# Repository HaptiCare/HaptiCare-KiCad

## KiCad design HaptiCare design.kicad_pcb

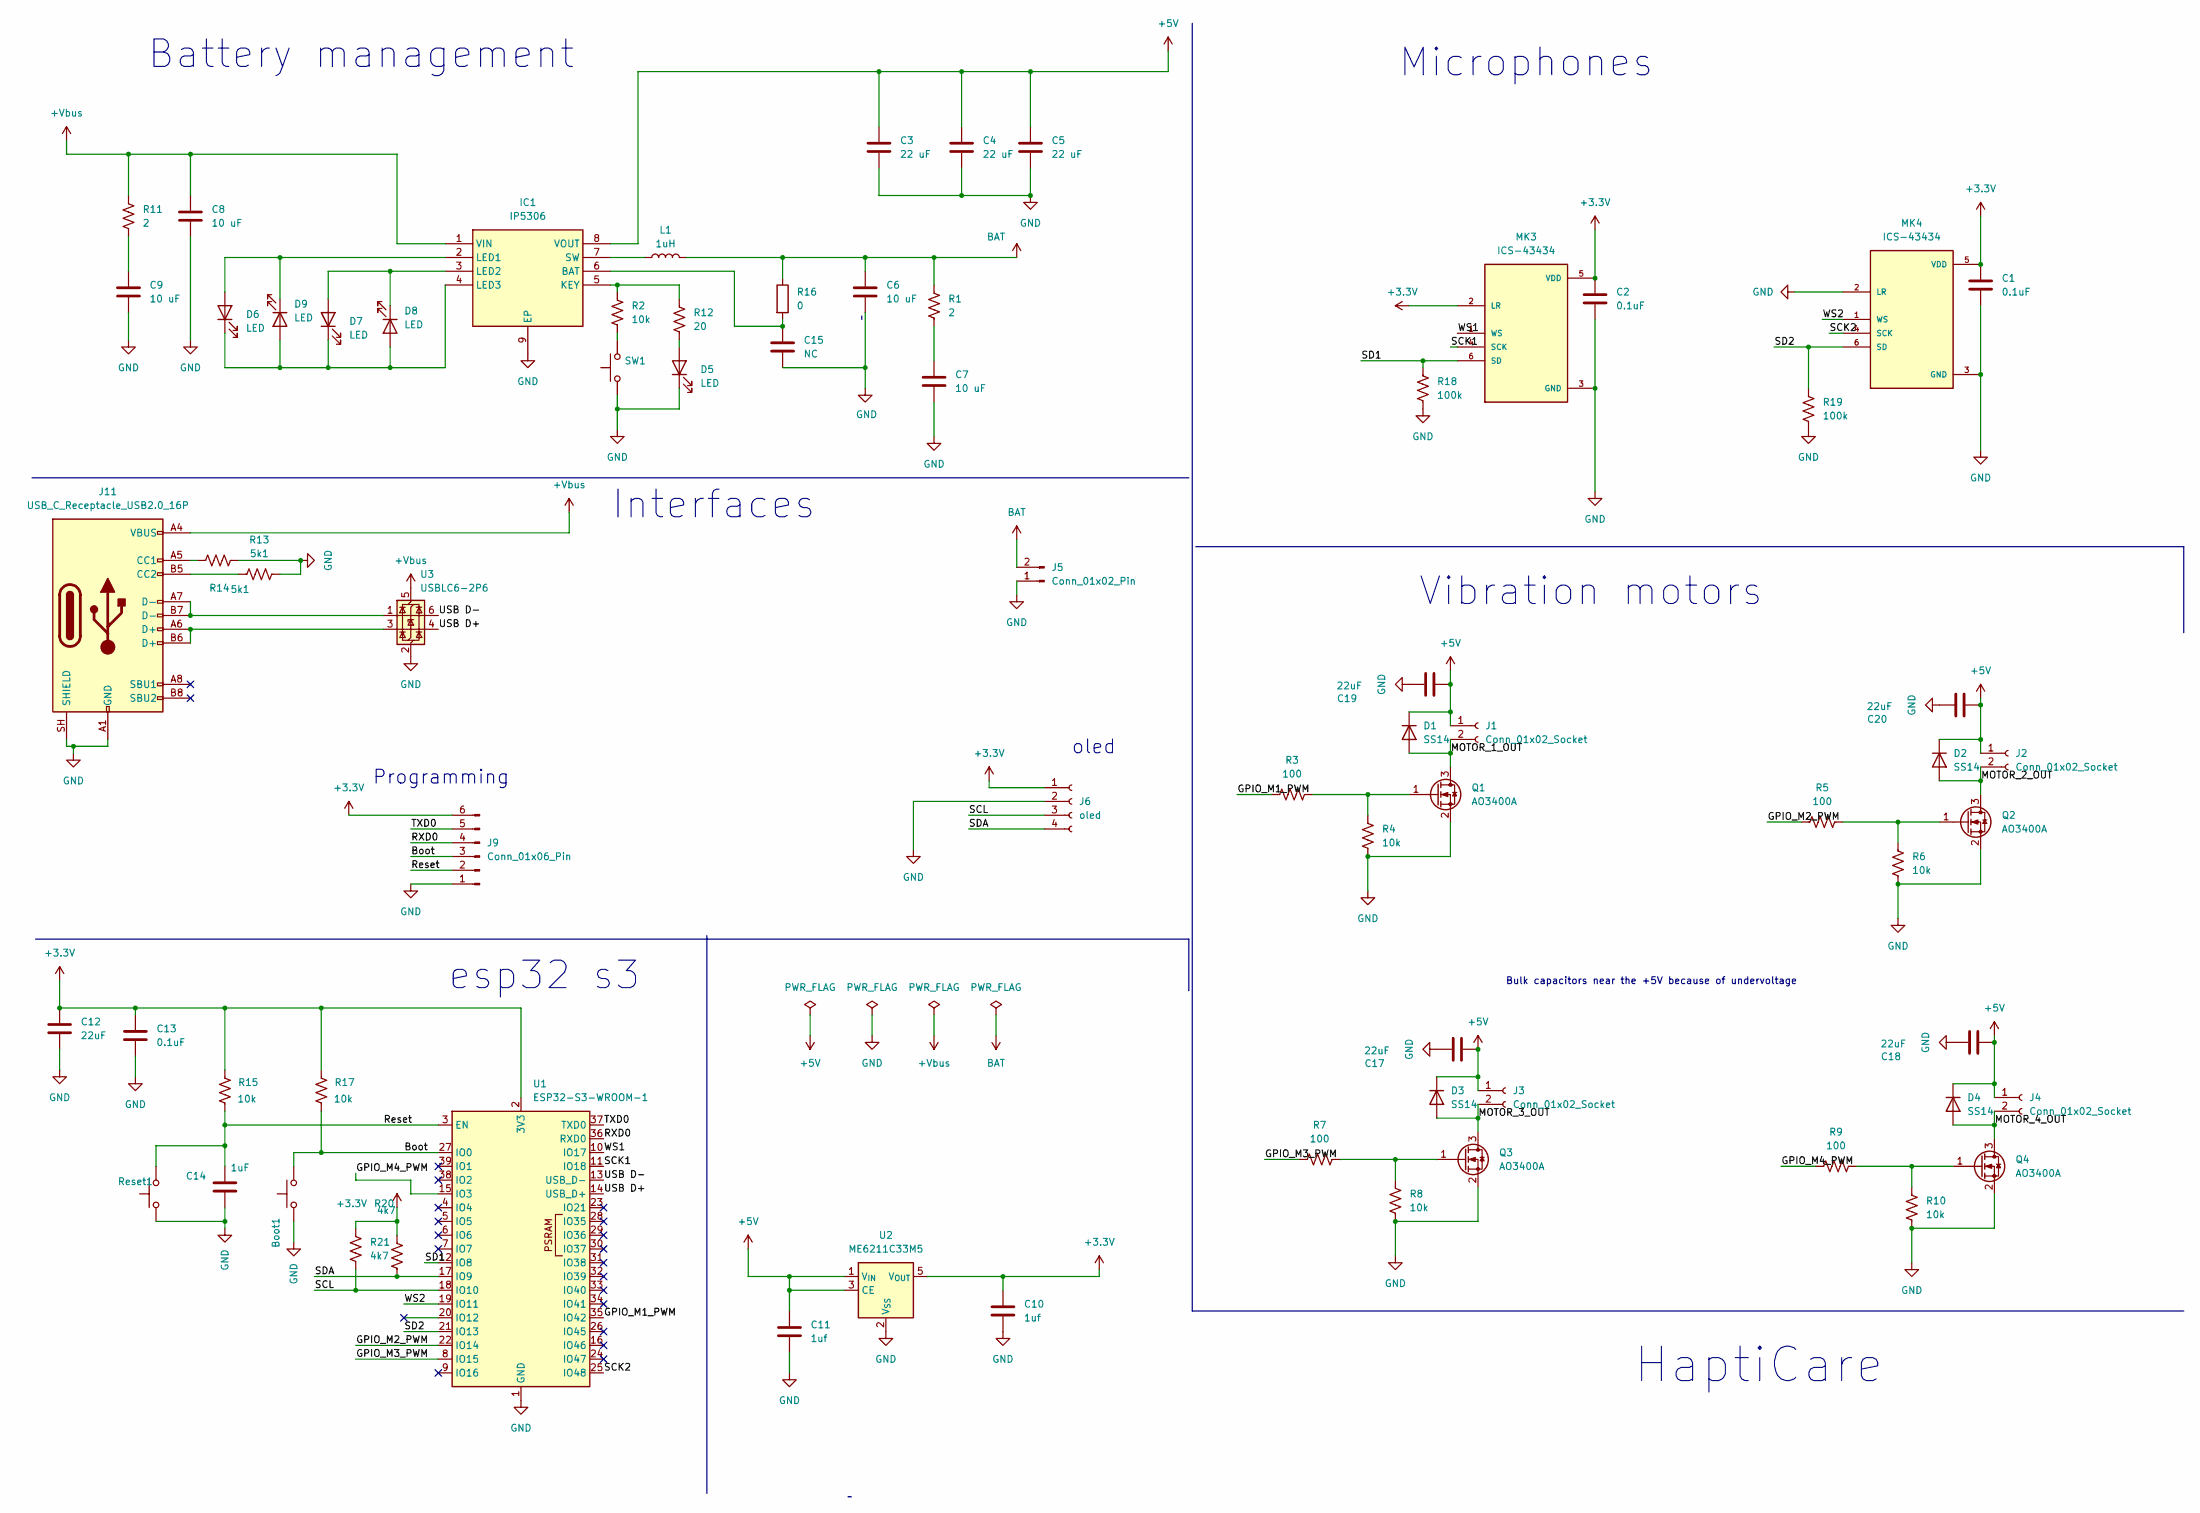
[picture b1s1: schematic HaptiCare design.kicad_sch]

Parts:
Boot1: SW_Push; SW_SPST_Omron_B3FS-100xP
C1, C2, C13: 0.1uF; C_0805_2012Metric
C3, C4, C5: 22 uF; C_0805_2012Metric
C6, C7, C8, C9: 10 uF; C_0805_2012Metric
C10, C11: 1uf; C_0805_2012Metric
C12, C17, C18, C19, C20: 22uF; C_0805_2012Metric
C14: 1uF; C_0805_2012Metric
C15: NC; C_0805_2012Metric
D1, D2, D3, D4: SS14; D_SMA
D5, D6, D7, D8, D9: LED; LED_0805_2012Metric
IC1: IP5306; SOIC127P600X165-9N; Manufacturer_Part_Number IP5306
J1, J2, J3, J4: Conn_01x02_Socket; JST_PH_B2B-PH-K_1x02_P2.00mm_Vertical
J5: Conn_01x02_Pin; PinSocket_1x02_P2.54mm_Vertical
J6: oled; PinSocket_1x04_P2.54mm_Vertical
J9: Conn_01x06_Pin; PinSocket_1x06_P2.54mm_Vertical
J11: USB_C_Receptacle_USB2.0_16P; USB_C_Receptacle_GCT_USB4105-xx-A_16P_TopMnt_Horizontal
L1: 1uH; L_Coilcraft_XxL4020
MK3, MK4: ICS-43434; MIC_ICS-43434
Q1, Q2, Q3, Q4: AO3400A; SOT-23
R1, R11: 2; R_0805_2012Metric
R2, R4, R6, R8, R10, R15, R17: 10k; R_0805_2012Metric
R3, R5, R7, R9: 100; R_0805_2012Metric
R12: 20; R_0805_2012Metric
R13, R14: 5k1; R_0805_2012Metric
R16: 0; R_0805_2012Metric
R18, R19: 100k; R_0805_2012Metric
R20, R21: 4k7; R_0805_2012Metric
Reset1: SW_Push; SW_SPST_Omron_B3FS-100xP
SW1: SW_Push; SW_SPST_Omron_B3FS-100xP
U1: ESP32-S3-WROOM-1
U2: ME6211C33M5; SOT-23-5
U3: USBLC6-2P6; SOT-666

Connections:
+3.3V: C1.1, C2.1, C10.1, C12.1, C13.1, J6.1, J9.6, MK3.2 (LR), MK3.5 (VDD), MK4.5 (VDD), R15.2, R17.2, R20.2, R21.2, U1.2 (3V3), U2.5 (V_{OUT})
+5V: C3.1, C4.1, C5.1, C11.1, C17.1, C18.1, C19.1, C20.1, D1.1 (K), D2.1 (K), D3.1 (K), D4.1 (K), IC1.8 (VOUT), J1.1, J2.1, J3.1, J4.1, U2.1 (V_{IN}), U2.3 (CE)
+Vbus: C8.1, IC1.1 (VIN), J11.A4 (VBUS), J11.A9 (VBUS), J11.B4 (VBUS), J11.B9 (VBUS), R11.1, U3.5 (VBUS)
/Boot: Boot1.2, J9.3, R17.1, U1.27 (IO0)
/GPIO_M1_PWM: R3.1, U1.35 (IO42)
/GPIO_M2_PWM: R5.1, U1.22 (IO14)
/GPIO_M3_PWM: R7.1, U1.8 (IO15)
/GPIO_M4_PWM: R9.1, U1.15 (IO3)
/MOTOR_1_OUT: D1.2 (A), J1.2, Q1.3 (D)
/MOTOR_2_OUT: D2.2 (A), J2.2, Q2.3 (D)
/MOTOR_3_OUT: D3.2 (A), J3.2, Q3.3 (D)
/MOTOR_4_OUT: D4.2 (A), J4.2, Q4.3 (D)
/RXD0: J9.4, U1.36 (RXD0)
/Reset: C14.2, J9.2, R15.1, Reset1.2, U1.3 (EN)
/SCK1: MK3.4 (SCK), U1.11 (IO18)
/SCK2: MK4.4 (SCK), U1.25 (IO48)
/SCL: J6.3, R21.1, U1.18 (IO10)
/SD1: MK3.6 (SD), R18.1, U1.12 (IO8)
/SD2: MK4.6 (SD), R19.1, U1.21 (IO13)
/SDA: J6.4, R20.1, U1.17 (IO9)
/TXD0: J9.5, U1.37 (TXD0)
/USB D+: U1.14 (USB_D+), U3.4 (I/O2)
/USB D-: U1.13 (USB_D-), U3.6 (I/O1)
/WS1: MK3.1 (WS), U1.10 (IO17)
/WS2: MK4.1 (WS), U1.19 (IO11)
BAT: C6.1, J5.2, L1.2, R1.1, R16.1
GND: Boot1.1, C1.2, C2.2, C3.2, C4.2, C5.2, C6.2, C7.2, C8.2, C9.2, C10.2, C11.2, C12.2, C13.2, C14.1, C15.2, C17.2, C18.2, C19.2, C20.2, D5.1 (K), IC1.9 (EP), J5.1, J6.2, J9.1, J11.A1 (GND), J11.A12 (GND), J11.B1 (GND), J11.B12 (GND), J11.SH (SHIELD), MK3.3 (GND), MK4.2 (LR), MK4.3 (GND), Q1.2 (S), Q2.2 (S), Q3.2 (S), Q4.2 (S), R4.2, R6.2, R8.2, R10.2, R13.2, R14.2, R18.2, R19.2, Reset1.1, SW1.1, U1.1 (GND), U1.40 (GND), U1.41 (GND), U2.2 (V_{SS}), U3.2 (GND)
unnamed: C7.1, R1.2
unnamed: C9.1, R11.2
unnamed: D5.2 (A), R12.2
unnamed: D6.2 (A), D9.1 (K), IC1.2 (LED1)
unnamed: D6.1 (K), D7.1 (K), D8.2 (A), D9.2 (A), IC1.4 (LED3)
unnamed: D7.2 (A), D8.1 (K), IC1.3 (LED2)
unnamed: C15.1, IC1.6 (BAT), R16.2
unnamed: IC1.5 (KEY), R2.1, R12.1
unnamed: IC1.7 (SW), L1.1
unnamed: J11.A5 (CC1), R14.1
unnamed: J11.B5 (CC2), R13.1
unnamed: J11.A6 (D+), J11.B6 (D+), U3.3 (I/O2)
unnamed: J11.A7 (D-), J11.B7 (D-), U3.1 (I/O1)
unnamed: Q1.1 (G), R3.2, R4.1
unnamed: Q2.1 (G), R5.2, R6.1
unnamed: Q3.1 (G), R7.2, R8.1
unnamed: Q4.1 (G), R9.2, R10.1
unnamed: R2.2, SW1.2

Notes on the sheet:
Battery management
esp32 s3
Vibration motors
oled
HaptiCare
Microphones
Programming
Interfaces
Bulk capacitors near the +5V because of undervoltage

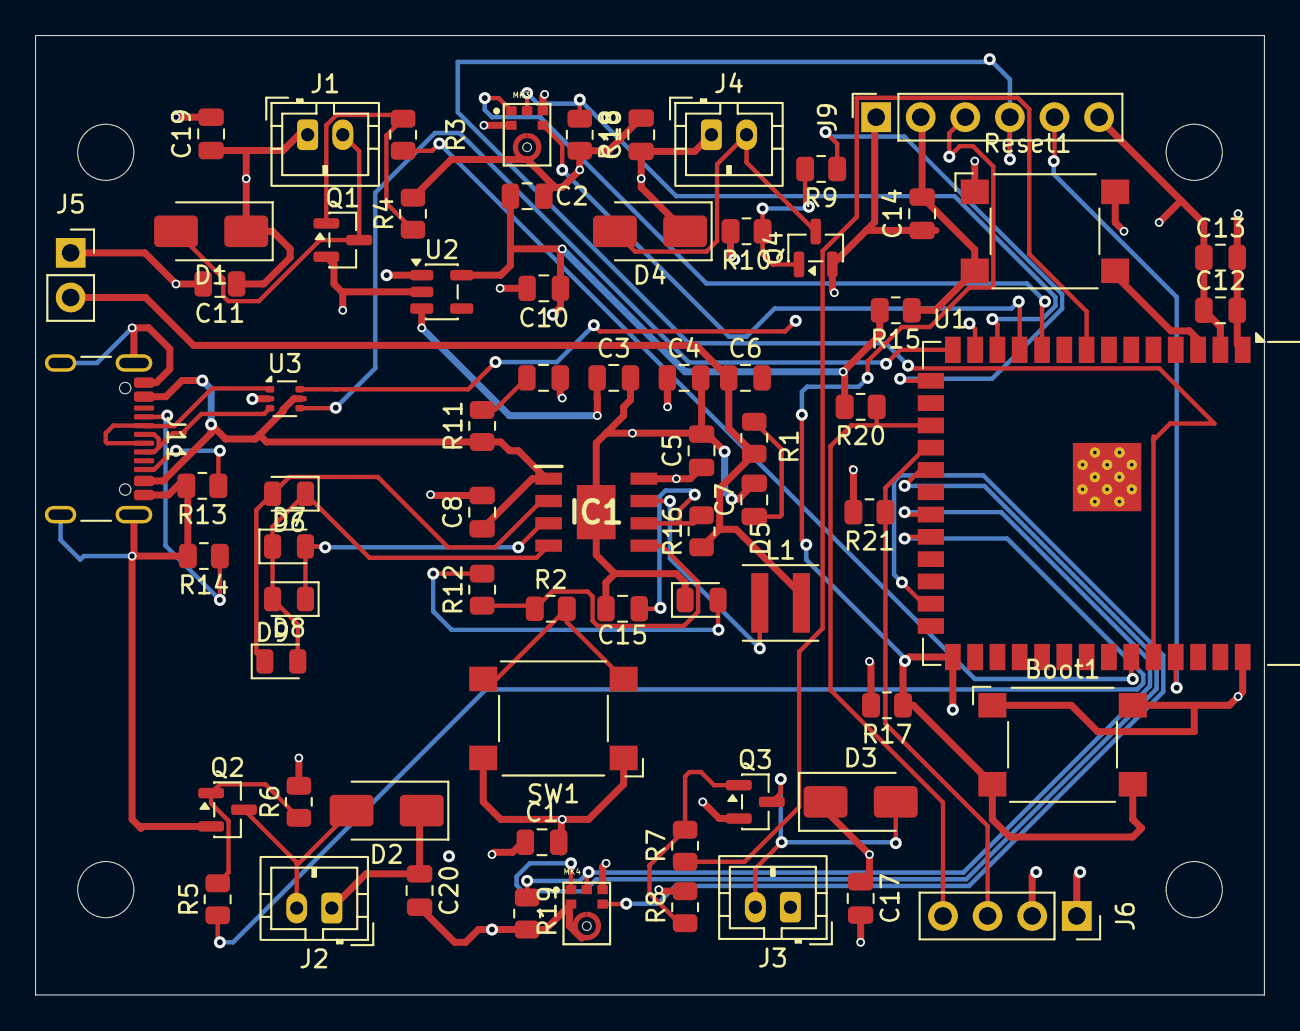
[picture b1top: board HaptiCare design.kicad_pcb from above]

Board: 4 copper layers, 70.0 x 54.7 mm, 71 parts (0 on the bottom side), 45 nets.
